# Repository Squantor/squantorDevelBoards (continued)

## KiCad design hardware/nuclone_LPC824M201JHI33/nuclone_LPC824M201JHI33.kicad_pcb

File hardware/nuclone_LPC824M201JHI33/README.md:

# Nuclone development board for LPC824M210JHI33
LPC824M210JHI33 development board inspired by the nucleo series from STM32.
## TODO's
Still some things need to be done:
* schematic entry (Done)
* PCB layout (Done)
* Review with one night in between (Done)
* Produce at [JLCPCB](https://jlcpcb.com/) (Done)
* Assemble (Done)
* Test & characterise (WIP)
* update Readme.md with pictures and BOM (WIP)

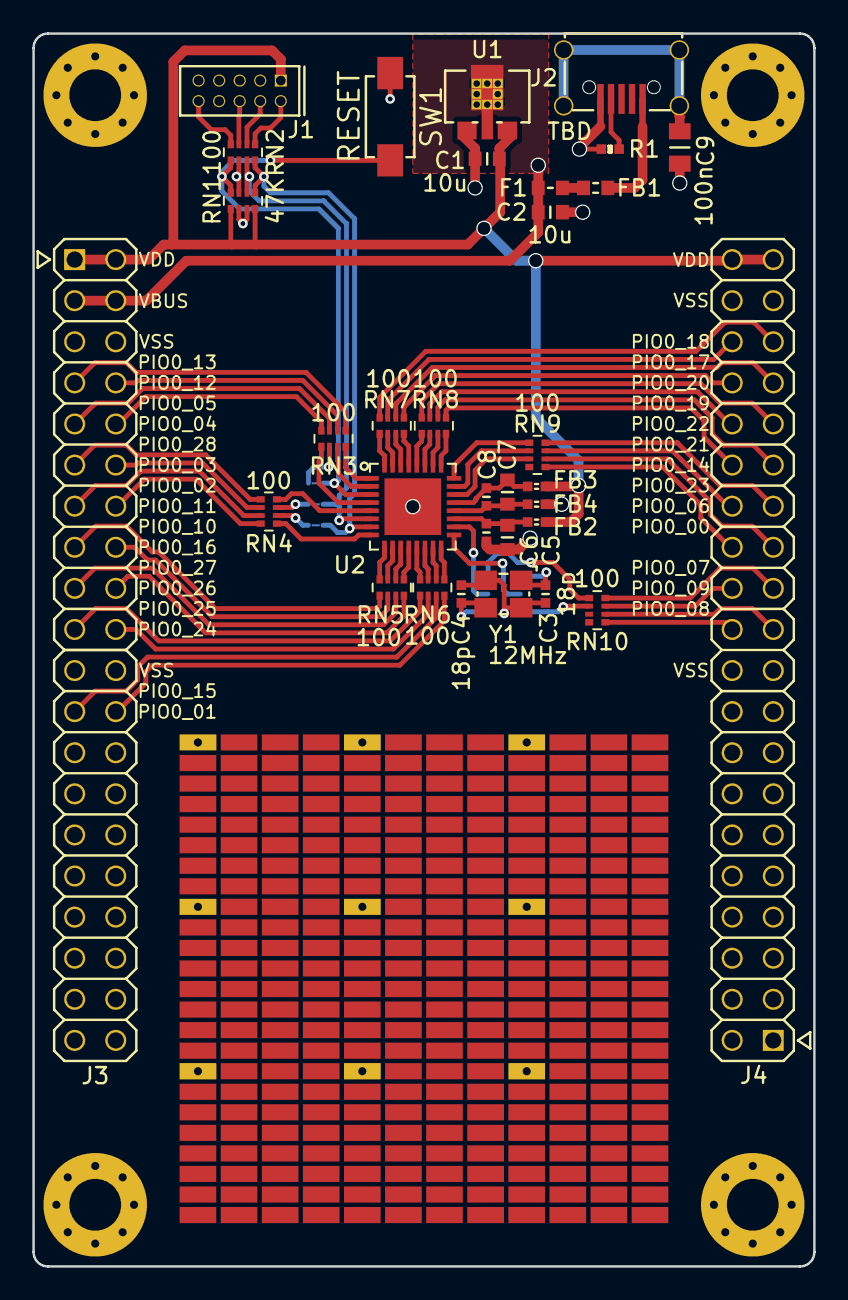
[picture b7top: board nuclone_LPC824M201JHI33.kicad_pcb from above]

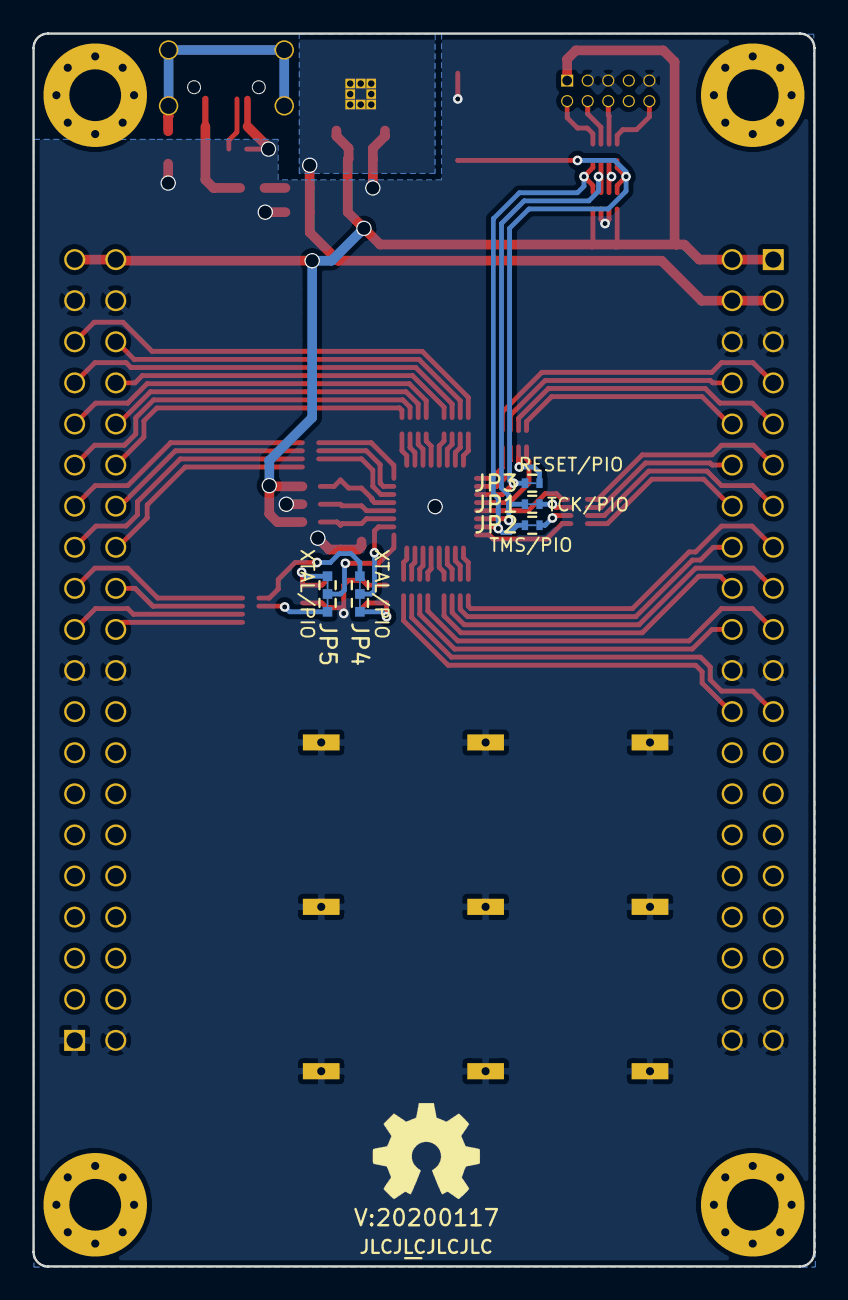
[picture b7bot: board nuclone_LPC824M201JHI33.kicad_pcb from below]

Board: 2 copper layers, 48.3 x 76.2 mm, 54 parts (8 on the bottom side), 83 nets.

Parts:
C1, C2, C5, C7: 10u; C_0603
C3, C4: 18p; C_0402
C6, C8: 1u; C_0402
C9: 100n; C_0805
F1: 0.5A; F_0603_hand
FB1: 100; L_0603
FB2, FB3, FB4: FB; L_0402
H1, H2, H3, H4: MountingHole; MountingHole_3.2mm_M3_Pad_Via
J1: JTAG_2X05; Header-0127-2X05-H006
J2: USB-ID; USB-muB-SMD_TH
J3: nuclone_small_left; nuclone_medium_left
J4: nuclone_small_right; nuclone_medium_right
J5, J6, J7, J8, J9, J10, J11, J12, J13: Proto_1pin; proto-SMD-0127-08X08-P010X020+pin
JP1: TCK/PIO; solder_jumper_2way_conn
JP2: TMS/PIO; solder_jumper_2way_conn
JP3: RESET/PIO; solder_jumper_2way_conn
JP4, JP5: XTAL/PIO; solder_jumper_3way_123conn
N1: OHWLOGO; OSHW-Symbol_6.7x6mm_SilkScreen
N2: 20200117; Label_version
N3: JLCJLCJLCJLC; Label_Generic
R1: TBD; R_0402_hand
RN1: 47K; R_Array_Convex_4x0402
RN2, RN3, RN4, RN5, RN6, RN7, RN8, RN9, RN10: 100; R_Array_Convex_4x0402
SW1: RESET; DTSM3
U1: MCP1702-MB; SOT89-SOT23-Dual-NXP
U2: LPC824M201JHI33; SOT617-3_alt_paste
Y1: 12MHz; Crystal_3225_4

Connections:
/GPIO_46: J4.21, RN10.6
/GPIO_47: J4.22, RN10.5
/GPIO_51: J4.26, RN9.5
/PIO0_0_MCU: RN9.1, U2.24
/PIO0_0_OUT: J4.27, RN9.8
/PIO0_1_MCU: RN6.1, U2.16
/PIO0_1_OUT: J3.24, RN6.8
/PIO0_2: JP2.1, RN4.2
/PIO0_2_MCU: JP2.2, RN1.5, RN2.8, U2.7
/PIO0_2_OUT: J3.13, RN4.7
/PIO0_3: JP1.1, RN4.3
/PIO0_3_MCU: JP1.2, RN1.6, RN2.7, U2.6
/PIO0_3_OUT: J3.12, RN4.6
/PIO0_4_MCU: RN3.1, U2.4
/PIO0_4_OUT: J3.10, RN3.8
/PIO0_5: JP3.1, RN3.2
/PIO0_5_MCU: JP3.2, RN1.8, RN2.5, SW1.2, U2.3
/PIO0_5_OUT: J3.9, RN3.7
/PIO0_6_MCU: RN9.2, U2.23
/PIO0_6_OUT: J4.28, RN9.7
/PIO0_7_MCU: RN9.3, U2.22
/PIO0_7_OUT: J4.25, RN9.6
/PIO0_8: JP4.1, RN10.1
/PIO0_8_MCU: JP4.2, U2.18
/PIO0_8_OUT: J4.23, RN10.8
/PIO0_9: JP5.1, RN10.2
/PIO0_9_MCU: JP5.2, U2.17
/PIO0_9_OUT: J4.24, RN10.7
/PIO0_10_MCU: RN5.4, U2.9
/PIO0_10_OUT: J3.15, RN5.5
/PIO0_11_MCU: RN4.1, U2.8
/PIO0_11_OUT: J3.14, RN4.8
/PIO0_12_MCU: RN3.3, U2.2
/PIO0_12_OUT: J3.8, RN3.6
/PIO0_13_MCU: RN3.4, U2.1
/PIO0_13_OUT: J3.7, RN3.5
/PIO0_14_MCU: RN8.4, U2.25
/PIO0_14_OUT: J4.30, RN8.5
/PIO0_15_MCU: RN6.2, U2.15
/PIO0_15_OUT: J3.23, RN6.7
/PIO0_16_MCU: RN5.3, U2.10
/PIO0_16_OUT: J3.16, RN5.6
/PIO0_17_MCU: RN7.1, U2.32
/PIO0_17_OUT: J4.35, RN7.8
/PIO0_18_MCU: RN7.2, U2.31
/PIO0_18_OUT: J4.36, RN7.7
/PIO0_19_MCU: RN7.3, U2.30
/PIO0_19_OUT: J4.33, RN7.6
/PIO0_20_MCU: RN7.4, U2.29
/PIO0_20_OUT: J4.34, RN7.5
/PIO0_21_MCU: RN8.1, U2.28
/PIO0_21_OUT: J4.31, RN8.8
/PIO0_22_MCU: RN8.2, U2.27
/PIO0_22_OUT: J4.32, RN8.7
/PIO0_23_MCU: RN8.3, U2.26
/PIO0_23_OUT: J4.29, RN8.6
/PIO0_24_MCU: RN6.3, U2.14
/PIO0_24_OUT: J3.20, RN6.6
/PIO0_25_MCU: RN6.4, U2.13
/PIO0_25_OUT: J3.19, RN6.5
/PIO0_26_MCU: RN5.1, U2.12
/PIO0_26_OUT: J3.18, RN5.8
/PIO0_27_MCU: RN5.2, U2.11
/PIO0_27_OUT: J3.17, RN5.7
/PIO0_28_MCU: RN4.4, U2.5
/PIO0_28_OUT: J3.11, RN4.5
/SWO_TDO: RN1.7, RN2.6
/VBUS: C2.2, F1.1, J3.3, J3.4, U1.2
/VDD: C1.1, FB2.2, FB3.2, J1.1, J3.1, J3.2, J4.39, J4.40, RN1.1, RN1.4, U1.3
/XTAL_IN: C3.1, JP5.3, Y1.1
/XTAL_OUT: C4.1, JP4.3, Y1.3
unnamed: C5.1, C6.1, FB2.1, U2.19
unnamed: C7.1, C8.1, FB3.1, U2.21
unnamed: C7.2, C8.2, FB4.1, U2.20
unnamed: C9.2, J2.S
unnamed: F1.2, FB1.1
unnamed: FB1.2, J2.1
unnamed: J1.2, RN2.1
unnamed: J1.4, RN2.2
unnamed: J1.6, RN2.3
unnamed: J1.10, RN2.4
unnamed: J2.4, R1.2
VSS: C1.2, C2.1, C3.2, C4.2, C5.2, C6.2, C9.1, FB4.2, J1.3, J1.5, J1.9, J2.5, J3.5, J3.6, J3.21, J3.22, J3.39, J3.40, J4.1, J4.2, J4.19, J4.20, J4.37, J4.38, J5.1, J6.1, J7.1, J8.1, J9.1, J10.1, J11.1, J12.1, J13.1, R1.1, RN1.2, RN1.3, SW1.1, U1.1, U2.33, Y1.2, Y1.4
